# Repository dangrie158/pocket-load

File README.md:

# Pocket Load

A small electronic dummy load for up to 40V / 6A. 
Further details are added as development progresses;

# Current Status

- Schematic: done
- Board: basically done (waiting for components to verify footprints)
- Firmware: in development (Libraries for Display, ADC, and some smaller interface components done)
- Prototype: board layout will be sent to fab as soon as components arrive
- Specification: Power dissipation ability and accuracy  will be testet as soon as prototype is ready
- Documentation: will be created during development

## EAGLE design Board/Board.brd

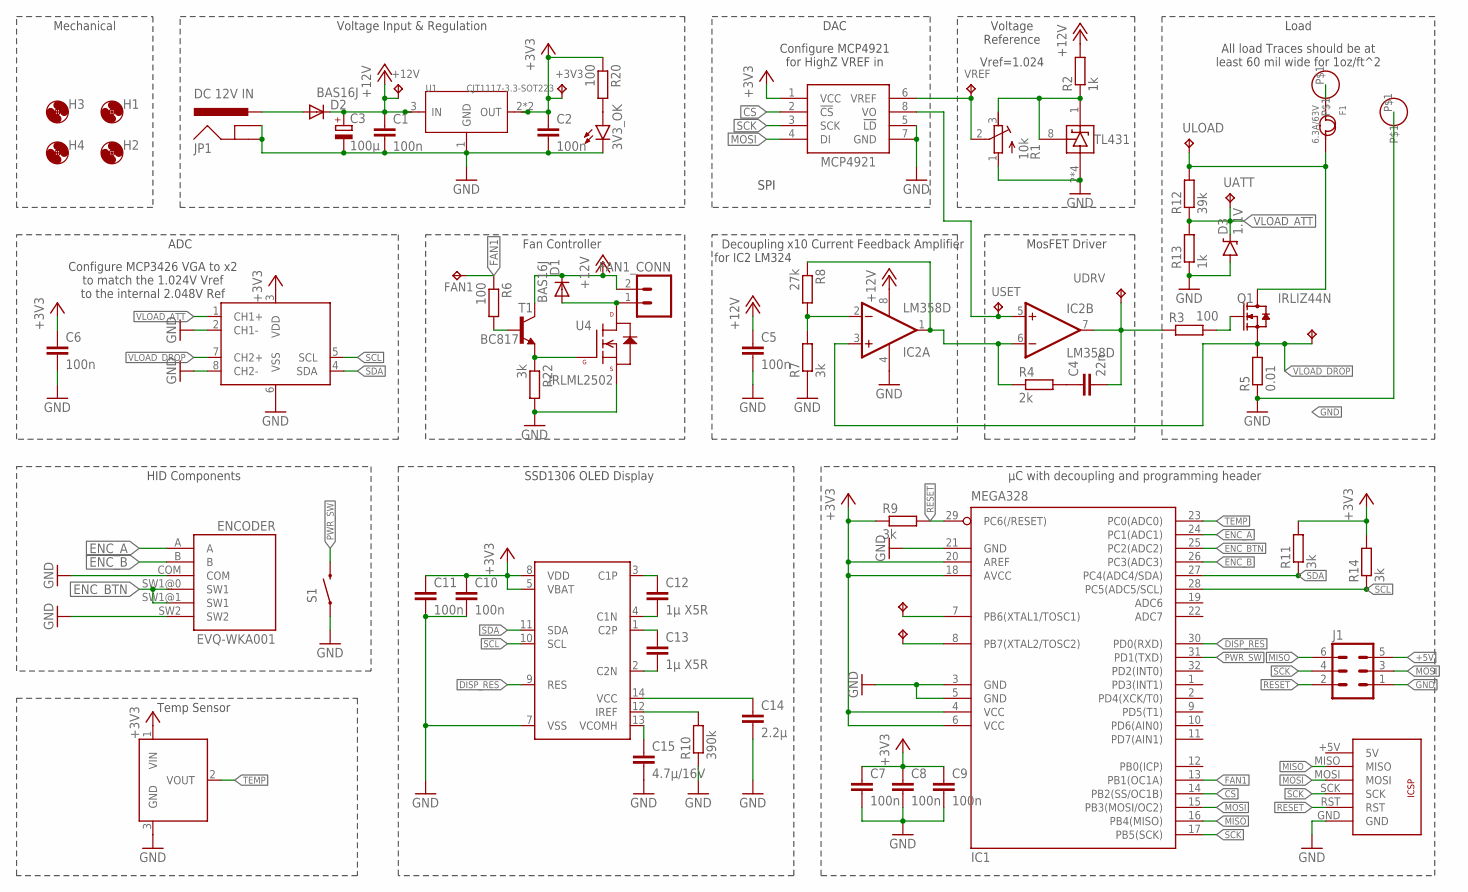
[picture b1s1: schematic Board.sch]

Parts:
3V3_OK: LED0603; LED-0603
+3V3, +12V: TPB1,27; B1,27
C1, C2, C5, C6, C7, C8, C9, C10, C11: 100n; C0603
C3: 100µ; 153CLV-0405
C4: 22n; C0603
C12, C13: 1µ X5R; C0603
C14: 2.2µ; C0603
C15: 4.7µ/16V; C0603
D1, D2: BAS16J; SOD323-W
D3: 1.1V; SOD-323
ENCODER: EVQ-WKA001
F1: 6.3A/63V; F1206
FAN1: TPB1,27; B1,27
FAN1_CONN: M02POLAR; MOLEX-1X2
H1, H2, H3, H4: MOUNT-HOLE3.0; 3,0
IC1: MEGA328; TQFP32-08
IC2: LM358D; SO08
IC4: MCP3426; SO08
IC6: MCP4921; SO-8
IC7: TL431CD; SO-8
IN+: 6MM-BANANA-MOUNTINGHOLE; 6MM-BANANA-MOUNT
IN-: 6MM-BANANA-MOUNTINGHOLE; 6MM-BANANA-MOUNT
J1: MA03-2
JP1: DC 12V IN; POWER_JACK_PTH
Q1: IRLIZ44N; TO-220H
R1: 10k; RTRIM3296W
R2, R13: 1k; R0603
R3, R6, R20: 100; R0603
R4: 2k; R0603
R5: 0.01; R2512
R7, R9, R11, R14, R22: 3k; R0603
R8: 27k; R0603
R10: 390k; R0603
R12: 39k; R0603
S1: SWITCH-MOMENTARY-2SMD-1101NE; TACTILE-SWITCH-1101NE
T1: BC817; SOT23-BEC
U1: CJT1117-3.3-SOT223; SOT-223
U3: MCP9701AT-E/TT; SOT32-3
U4: IRLML2502; SOT23-3
U$2: 0.86"-OLEDBENT; 0.86"-OLED-BENT
U$4: ICSP; ICSP-SMD-NOSILK
UATT: TPB1,27; B1,27
UDROP: TPB1,27; B1,27
UDRV: TPB1,27; B1,27
ULOAD: TPB1,27; B1,27
USET: TPB1,27; B1,27
VREF: TPB1,27; B1,27
XTAL1, XTAL2: TPB1,27; B1,27

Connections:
+3V3: +3V3.TP, C2.1, C6.1, C7.1, C8.1, C9.1, C10.1, C11.1, IC1.4 (VCC), IC1.6 (VCC), IC1.18 (AVCC), IC1.20 (AREF), IC4.3 (VDD), IC6.1 (VCC), R9.1, R11.2, R14.2, R20.1, U1.2 (OUT), U1.TER (OUT), U3.1 (VIN), U$2.5 (VBAT), U$2.8 (VDD)
+5V: J1.5
+12V: +12V.TP, C1.1, C3.+, C5.1, D1.C, D2.C, FAN1_CONN.2, IC2.8 (V+), R2.2, T1.C, U1.3 (IN)
CS: IC1.14 (PB2(SS/OC1B)), IC6.2 (!CS!)
DISP_RES: IC1.30 (PD0(RXD)), U$2.9 (RES)
ENC_A: ENCODER.A, IC1.24 (PC1(ADC1))
ENC_B: ENCODER.B, IC1.26 (PC3(ADC3))
ENC_BTN: ENCODER.SW1@0 (SW1), ENCODER.SW1@1 (SW1), IC1.25 (PC2(ADC2))
FAN1: FAN1.TP, IC1.13 (PB1(OC1A)), R6.1
GND: 3V3_OK.C, C1.2, C2.2, C3.-, C5.2, C6.2, C7.2, C8.2, C9.2, C10.2, C11.2, C14.2, C15.2, D3.A, ENCODER.COM, ENCODER.SW2, IC1.3 (GND), IC1.5 (GND), IC1.21 (GND), IC2.4 (V-), IC4.2 (CH1-), IC4.6 (VSS), IC4.8 (CH2-), IC6.5 (!LD!), IC6.7 (GND), IC7.2 (ANODE), IC7.3 (ANODE), IC7.6 (ANODE), IC7.7 (ANODE), IN-.P$1, J1.1, JP1.GND, JP1.GNDBREAK, R1.1 (A), R5.1, R7.1, R10.1, R13.1, R22.2, S1.1, U1.1 (GND), U3.3 (GND), U4.2 (S), U$2.7 (VSS), U$4.GND
LOAD+: F1.2, Q1.P$2 (D), R12.2, ULOAD.TP
MISO: IC1.16 (PB4(MISO)), J1.6, U$4.MISO
MOSI: IC1.15 (PB3(MOSI/OC2)), IC6.4 (DI), J1.3, U$4.MOSI
unnamed: IC7.1 (CATHODE), IC7.8 (REF), R1.3 (E), R2.1
unnamed: IC6.6 (VREF), R1.2 (S), VREF.TP
unnamed: C4.1, R4.2
unnamed: R22.1, T1.E, U4.1 (G)
unnamed: D1.A, FAN1_CONN.1, U4.3 (D)
unnamed: Q1.P$1 (G), R3.2
unnamed: F1.1, IN+.P$1
unnamed: R6.2, T1.B
unnamed: IC2.1 (OUT), IC2.6 (-IN), R4.1, R8.1
unnamed: C4.2, IC2.7 (OUT), R3.1, UDRV.TP
unnamed: IC2.2 (-IN), R7.2, R8.2
unnamed: IC1.8 (PB7(XTAL2/TOSC2)), XTAL2.TP
unnamed: IC1.7 (PB6(XTAL1/TOSC1)), XTAL1.TP
unnamed: C12.1, U$2.3 (C1P)
unnamed: C12.2, U$2.4 (C1N)
unnamed: C13.1, U$2.1 (C2P)
unnamed: C13.2, U$2.2 (C2N)
unnamed: C15.1, U$2.13 (VCOMH)
unnamed: R10.2, U$2.12 (IREF)
unnamed: C14.1, U$2.14 (VCC)
unnamed: 3V3_OK.A, R20.2
PWR_SW: IC1.31 (PD1(TXD)), S1.2
RESET: IC1.29 (PC6(/RESET)), J1.2, R9.2, U$4.RST
SCK: IC1.17 (PB5(SCK)), IC6.3 (SCK), J1.4, U$4.SCK
SCL: IC1.28 (PC5(ADC5/SCL)), IC4.5 (SCL), R14.1, U$2.10 (SCL)
SDA: IC1.27 (PC4(ADC4/SDA)), IC4.4 (SDA), R11.1, U$2.11 (SDA)
TEMP: IC1.23 (PC0(ADC0)), U3.2 (VOUT)
VLOAD_ATT: D3.C, IC4.1 (CH1+), R12.1, R13.2, UATT.TP
VLOAD_DROP: IC2.3 (+IN), IC4.7 (CH2+), Q1.P$3 (S), R5.2, UDROP.TP
VLOAD_REF: IC2.5 (+IN), IC6.8 (VO), USET.TP
VSW: D2.A, JP1.PWR

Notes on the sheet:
x10 Current Feedback Amplifier
Decoupling for IC2 LM324
MosFET Driver
Load
Voltage Reference
DAC
Voltage Input & Regulation
Fan Controller
All load Traces should be at least 60 mil wide for 1oz/ft^2
SPI
Configure MCP4921 for HighZ VREF in
ADC
Mechanical
Vref=1.024
Configure MCP3426 VGA to x2 to match the 1.024V Vref to the internal 2.048V Ref
HID Components
Temp Sensor
SSD1306 OLED Display
µC with decoupling and programming header

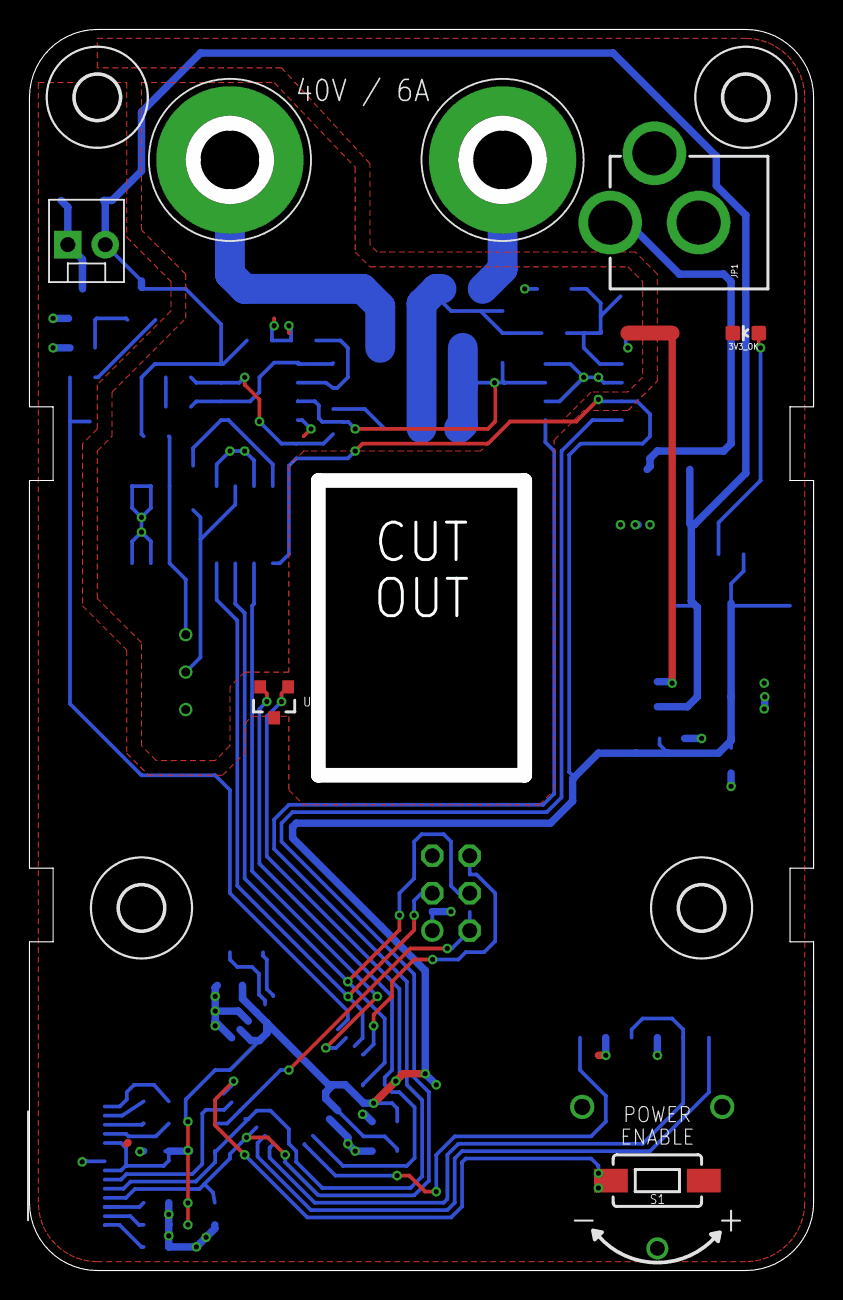
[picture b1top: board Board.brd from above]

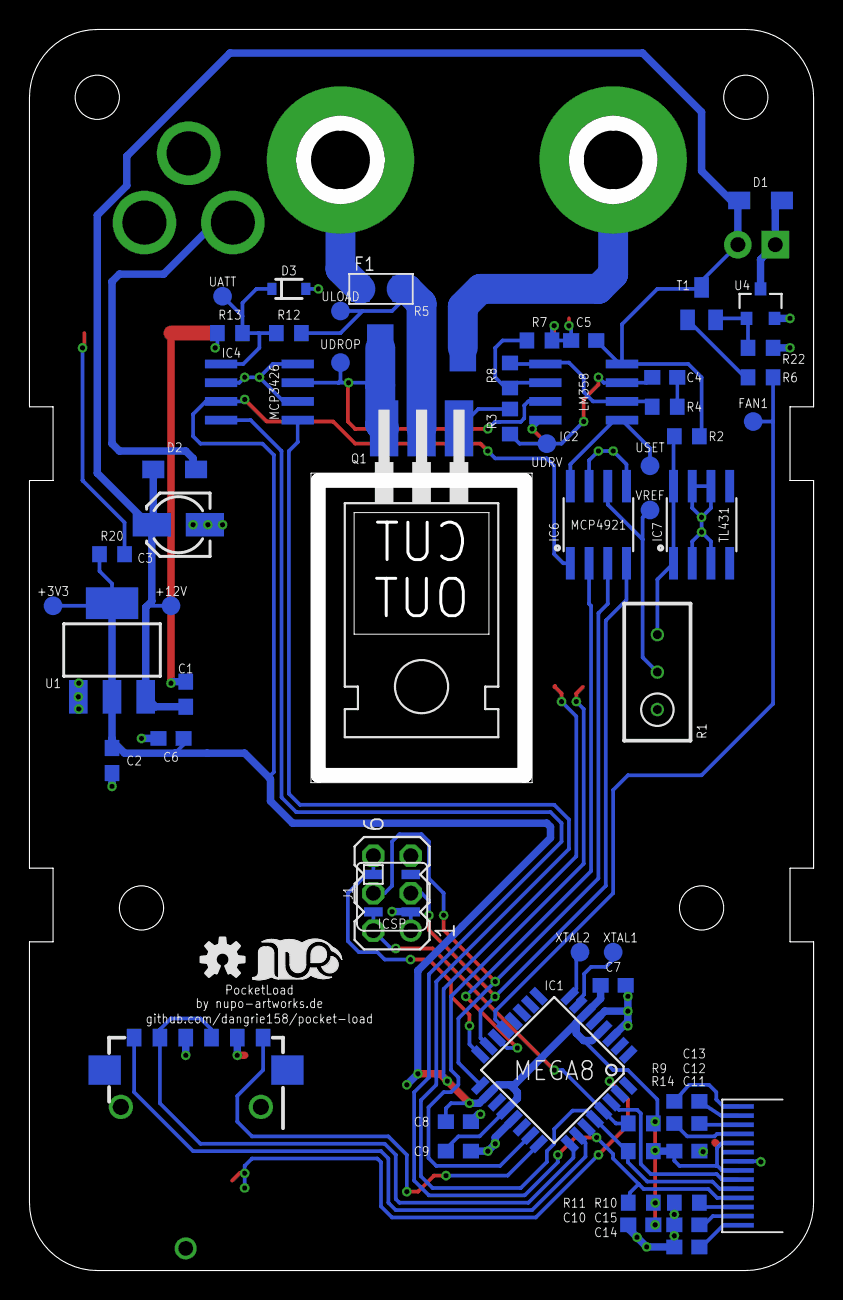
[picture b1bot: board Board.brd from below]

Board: 2 copper layers, 52.2 x 83.2 mm, 72 parts (60 on the bottom side), 43 nets.

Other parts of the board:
U$1: LOGO-SILKSCREEEN-S
U$3: OSHW-LOGO-S

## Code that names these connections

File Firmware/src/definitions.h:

#include <Arduino.h>

#define MCP4921_CS 10
#define ENC_A A1
#define ENC_B A3
#define ENC_BTN A2
#define BTN_PWR 1
#define FAN 9
#define TEMP_SENS A0

#define ENC_STEPS_PER_NOTCH 4

//software defined limits
#define T_MAX 90   // 90°C
#define I_MAX 6000 // 6A
#define U_MAX 4000 // 40V

#define FAN_TEMP_HIGH 30 //temperature at which the an switches on
#define FAN_TEMP_LOW 27 //temperature at which the an switches off again

//from MCP9701 datasheet
#define Tc 19.5f
#define V0 400

#define USEC_PER_HOUR 1000L * 60L * 60L

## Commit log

2017-10-01 added readme
2017-10-01 firmware improvements
2017-10-01 added thermal management code
2017-10-01 added nupo logo to bottom silkscreen
2017-10-01 fixed power on bug
2017-10-02 added OSHW logo
2017-10-03 added link to github repo
2017-10-03 improved thermal performance of temp sensor
2017-10-04 added zener to vload_att net to protect from overvoltage conditions
2017-10-18 added throughhole ICSP header
2017-10-18 added testpads for XTAL1 and XTAL2

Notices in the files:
parts and their libraries:
SparkFun-Connectors: Licensing: Creative Commons ShareAlike 4.0 International - https://creativecommons.org/licenses/by-sa/4.0
